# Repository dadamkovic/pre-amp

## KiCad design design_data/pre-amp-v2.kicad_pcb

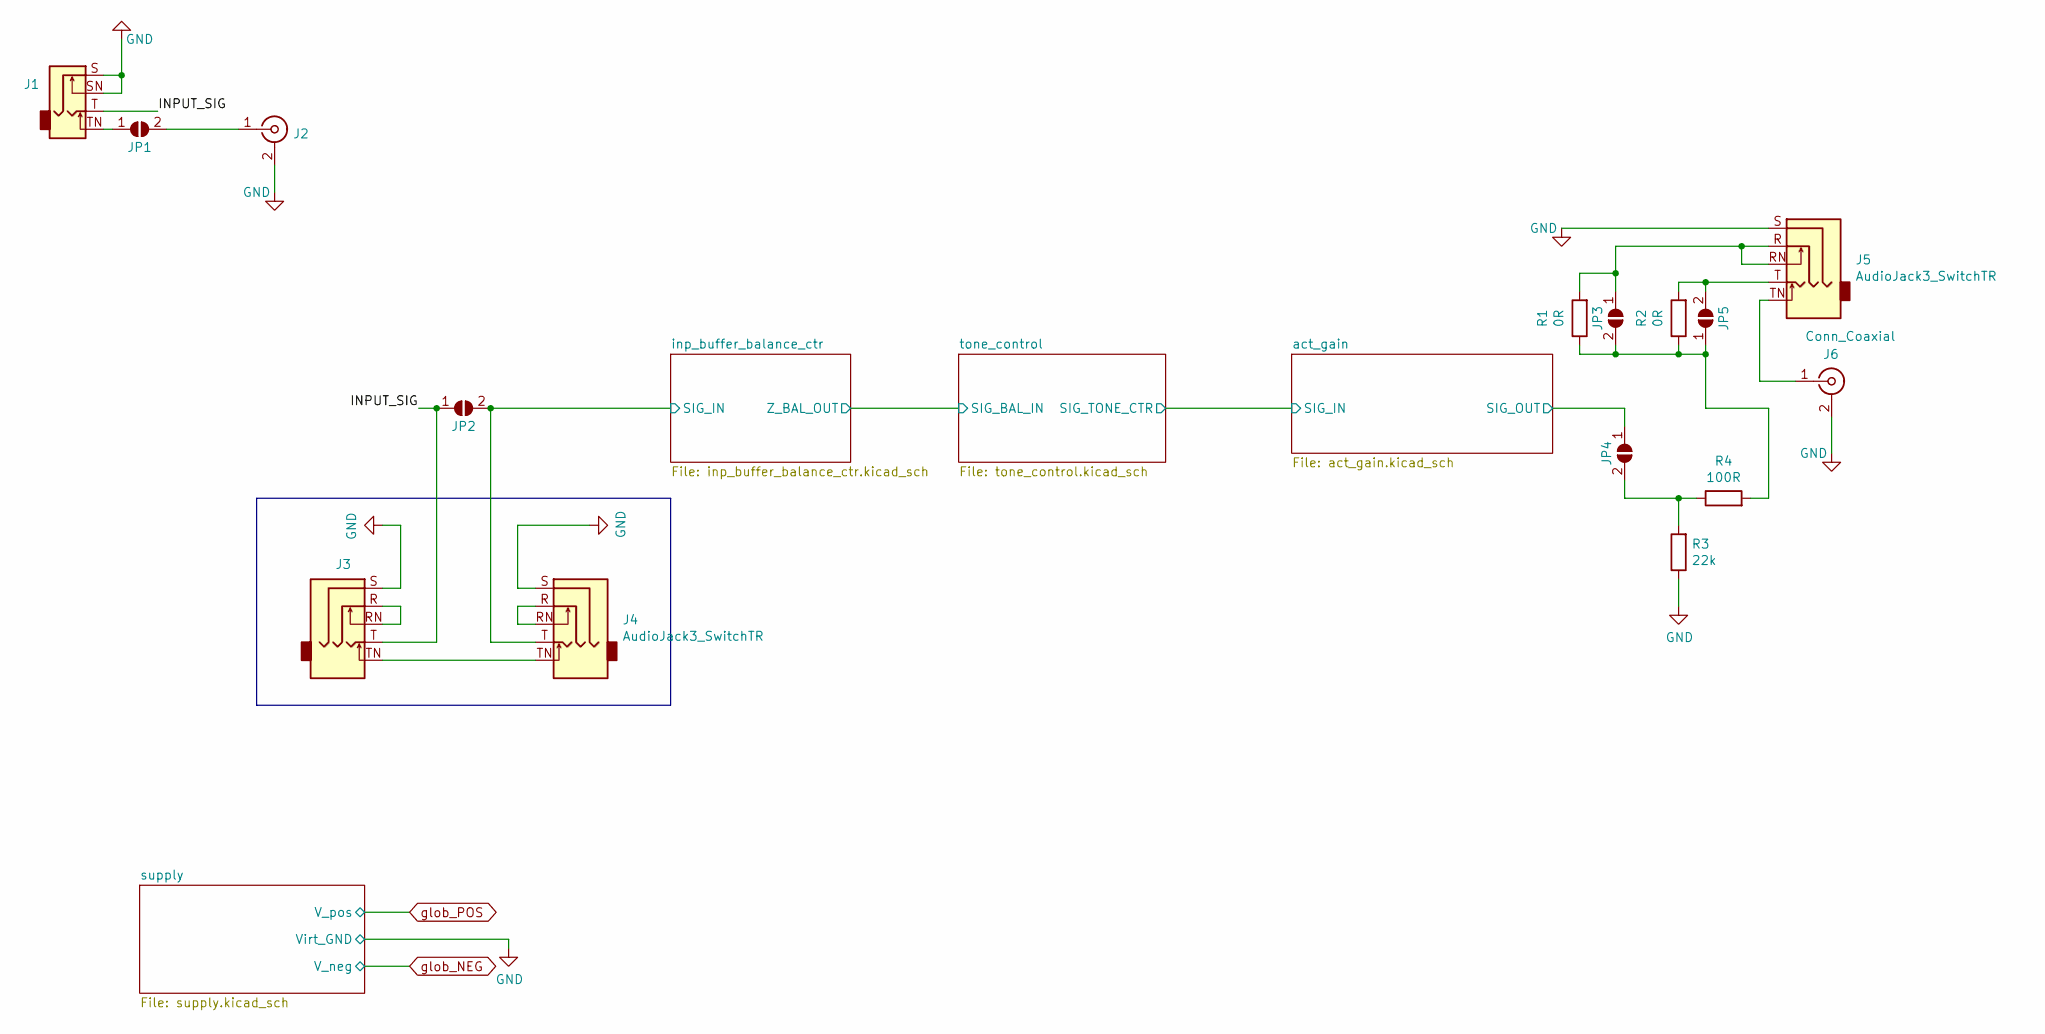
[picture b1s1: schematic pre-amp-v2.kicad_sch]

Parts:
J1: AudioJack2_Switch; Jack_6.35mm_Neutrik_NMJ4HHD2_Horizontal
J2, J6: Conn_Coaxial; 156-0096-E
J3, J4, J5: AudioJack3_SwitchTR; Jack_3.5mm_CUI_SJ1-3535NG_Horizontal
JP1, JP2, JP3, JP4, JP5: SolderJumper_2_Open; SolderJumper-2_P1.3mm_Open_RoundedPad1.0x1.5mm
R1, R2: 0R; R_0805_2012Metric_Pad1.20x1.40mm_HandSolder
R3: 22k; R_0805_2012Metric_Pad1.20x1.40mm_HandSolder
R4: 100R; R_0805_2012Metric_Pad1.20x1.40mm_HandSolder

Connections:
/INPUT_SIG: J1.T, J3.T, JP2.1 (A)
/act_gain/SIG_OUT: JP4.1 (A); also elsewhere on the board
/inp_buffer_balance_ctr/SIG_IN: J4.T, JP2.2 (B); also elsewhere on the board
GND: J1.S, J1.SN, J2.2 (Ext), J3.S, J4.S, J5.S, J6.2 (Ext), R3.1; also elsewhere on the board
unnamed: J1.TN, JP1.1 (A)
unnamed: J2.1 (In), JP1.2 (B)
unnamed: J3.R, J3.RN
unnamed: J3.TN, J4.TN
unnamed: J4.R, J4.RN
unnamed: J5.R, J5.RN, JP3.1 (A), R1.2
unnamed: J5.T, JP5.2 (B), R2.2
unnamed: J5.TN, J6.1 (In)
unnamed: JP3.2 (B), JP5.1 (A), R1.1, R2.1, R4.2
unnamed: JP4.2 (B), R3.2, R4.1

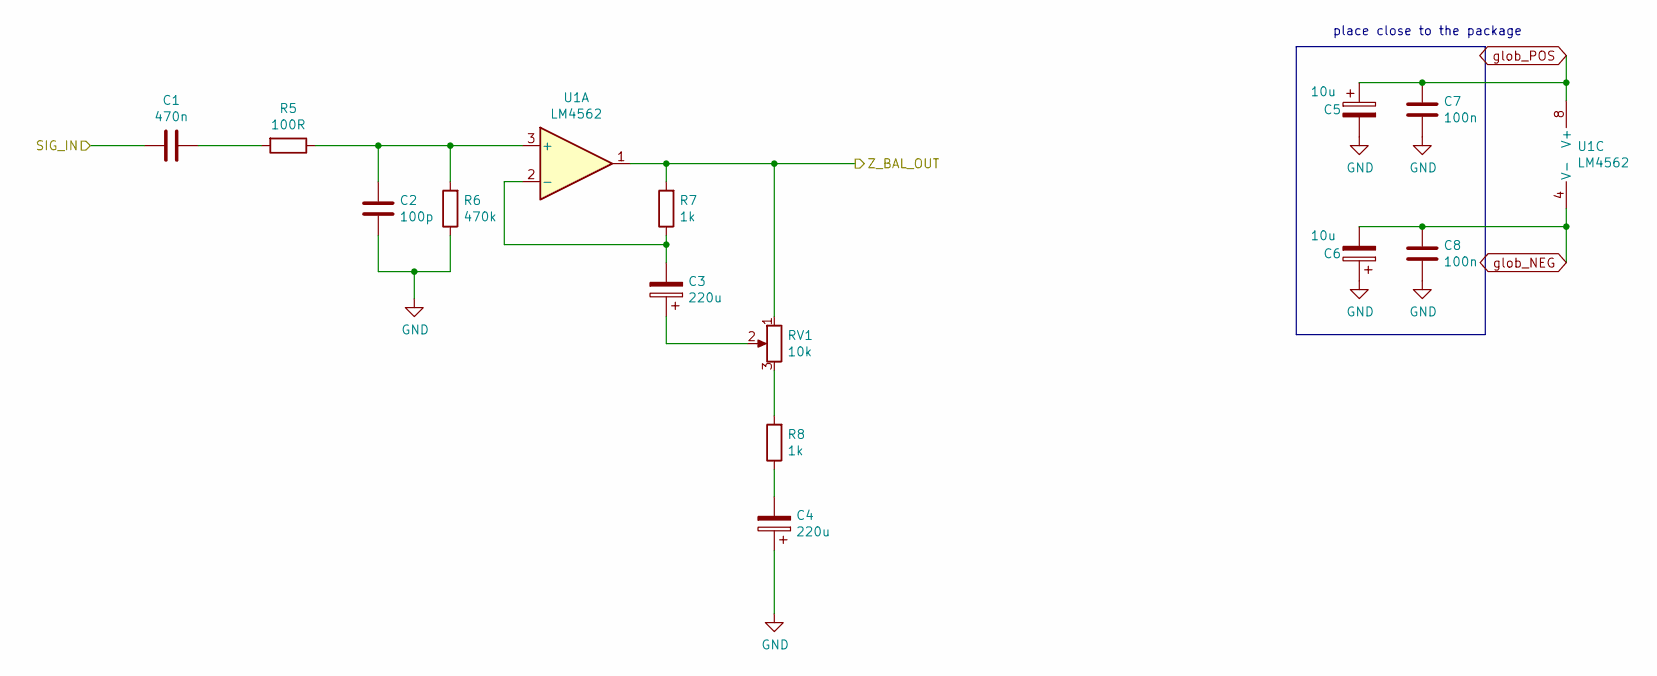
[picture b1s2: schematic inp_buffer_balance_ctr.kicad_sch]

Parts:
C1: 470n; C_Rect_L7.2mm_W3.5mm_P5.00mm_FKS2_FKP2_MKS2_MKP2
C2: 100p; C_0805_2012Metric_Pad1.18x1.45mm_HandSolder
C3, C4: 220u; CP_Radial_D6.3mm_P2.50mm
C5, C6: 10u; CP_Elec_4x5.4
C7, C8: 100n; C_0805_2012Metric_Pad1.18x1.45mm_HandSolder
R5: 100R; R_0805_2012Metric_Pad1.20x1.40mm_HandSolder
R6: 470k; R_0805_2012Metric_Pad1.20x1.40mm_HandSolder
R7, R8: 1k; R_0805_2012Metric_Pad1.20x1.40mm_HandSolder
RV1: 10k; Potentiometer_Bourns_PTV09A-1_Single_Vertical
U1: LM4562; SOIC-8_3.9x4.9mm_P1.27mm

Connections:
/inp_buffer_balance_ctr/SIG_IN: C1.2; also elsewhere on the board
/inp_buffer_balance_ctr/Z_BAL_OUT: R7.2, RV1.1, U1.1; also elsewhere on the board
GND: C2.1, C4.1, C5.2, C6.1, C7.2, C8.2, R6.1; also elsewhere on the board
unnamed: C1.1, R5.2
unnamed: C2.2, R5.1, R6.2, U1.3 (+)
unnamed: C3.1, RV1.2
unnamed: C3.2, R7.1, U1.2 (-)
unnamed: C4.2, R8.1
unnamed: R8.2, RV1.3
glob_NEG: C6.2, C8.1, U1.4 (V-); also elsewhere on the board
glob_POS: C5.1, C7.1, U1.8 (V+); also elsewhere on the board

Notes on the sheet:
place close to the package

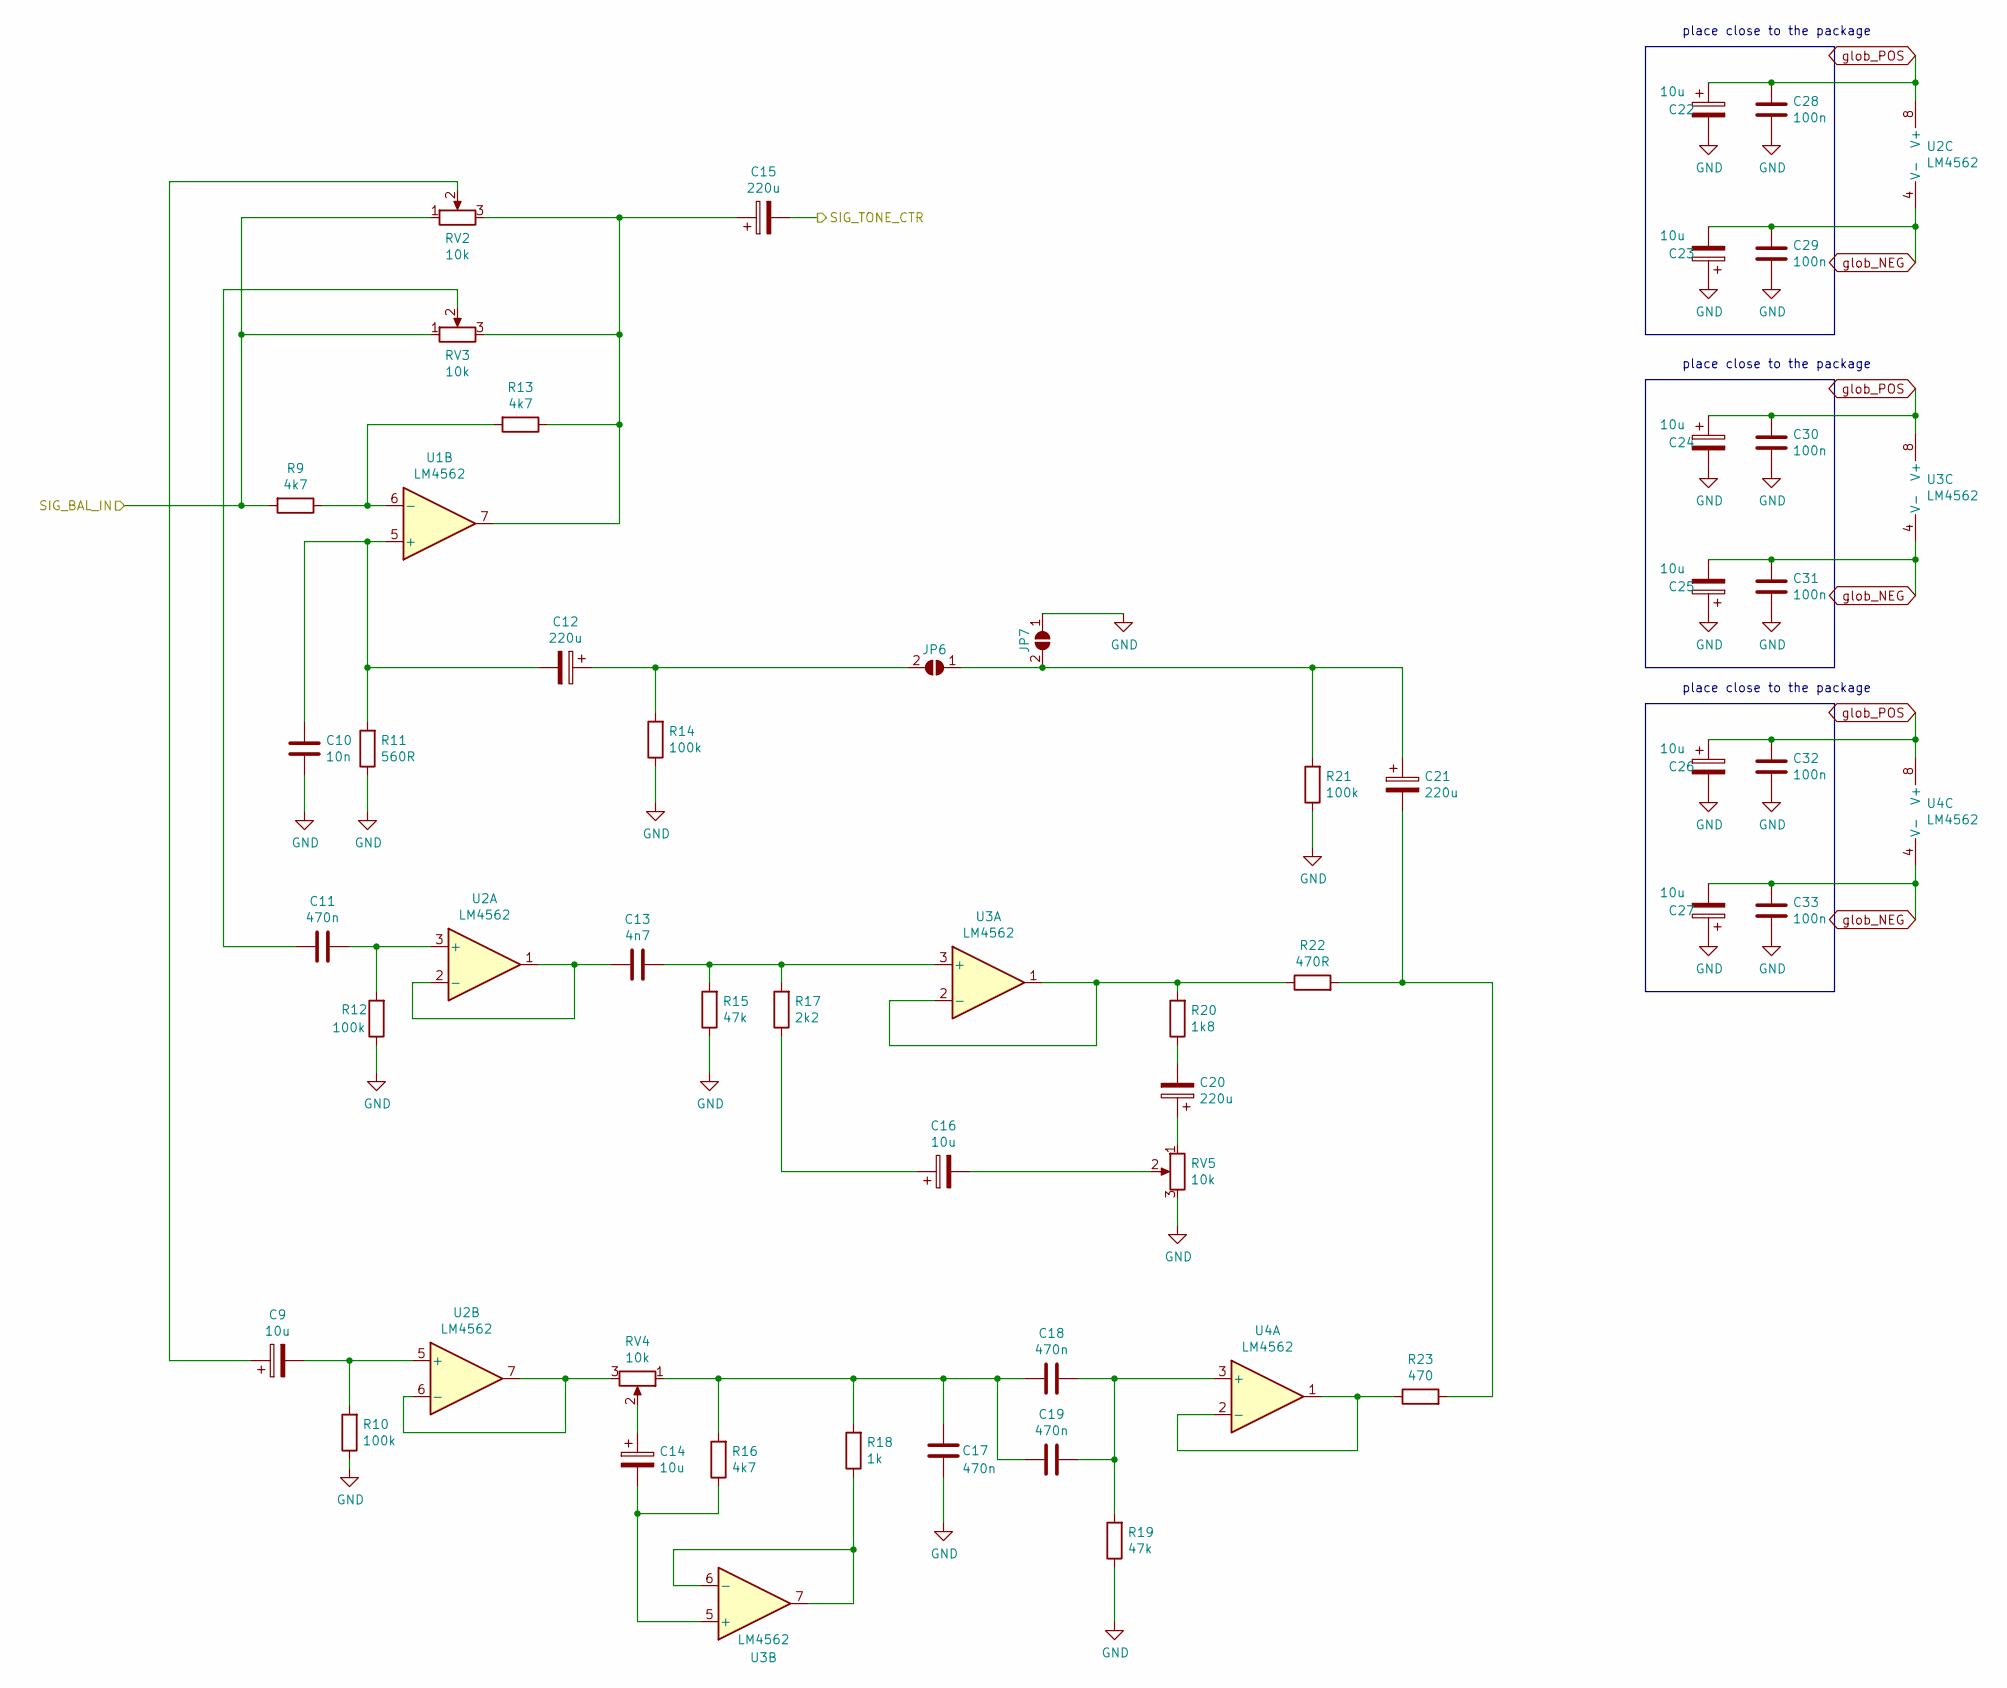
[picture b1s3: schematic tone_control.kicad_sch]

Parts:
C9, C14, C16, C22, C23, C24, C25, C26, C27: 10u; CP_Elec_4x5.4
C10: 10n; C_0805_2012Metric_Pad1.18x1.45mm_HandSolder
C11, C18, C19: 470n; C_Rect_L7.2mm_W3.5mm_P5.00mm_FKS2_FKP2_MKS2_MKP2
C12, C15, C20, C21: 220u; CP_Radial_D6.3mm_P2.50mm
C13: 4n7; C_0805_2012Metric_Pad1.18x1.45mm_HandSolder
C17: 470n; C_0805_2012Metric_Pad1.18x1.45mm_HandSolder
C28, C29, C30, C31, C32, C33: 100n; C_0805_2012Metric_Pad1.18x1.45mm_HandSolder
JP6, JP7: SolderJumper_2_Open; SolderJumper-2_P1.3mm_Open_RoundedPad1.0x1.5mm
R9, R13, R16: 4k7; R_0805_2012Metric_Pad1.20x1.40mm_HandSolder
R10, R12, R14, R21: 100k; R_0805_2012Metric_Pad1.20x1.40mm_HandSolder
R11: 560R; R_0805_2012Metric_Pad1.20x1.40mm_HandSolder
R15, R19: 47k; R_0805_2012Metric_Pad1.20x1.40mm_HandSolder
R17: 2k2; R_0805_2012Metric_Pad1.20x1.40mm_HandSolder
R18: 1k; R_0805_2012Metric_Pad1.20x1.40mm_HandSolder
R20: 1k8; R_0805_2012Metric_Pad1.20x1.40mm_HandSolder
R22: 470R; R_0805_2012Metric_Pad1.20x1.40mm_HandSolder
R23: 470; R_0805_2012Metric_Pad1.20x1.40mm_HandSolder
RV2, RV3: 10k; Potentiometer_Bourns_PTV09A-1_Single_Vertical
RV4, RV5: 10k; Potentiometer_Bourns_PTA6043_Single_Slide
U1, U2, U3, U4: LM4562; SOIC-8_3.9x4.9mm_P1.27mm

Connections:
/act_gain/SIG_IN: C15.2; also elsewhere on the board
/inp_buffer_balance_ctr/Z_BAL_OUT: R9.2, RV2.1, RV3.1; also elsewhere on the board
GND: C10.1, C17.2, C22.2, C23.1, C24.2, C25.1, C26.2, C27.1, C28.2, C29.2, C30.2, C31.2, C32.2, C33.2, JP7.1 (A), R10.1, R11.1, R12.1, R14.1, R15.1, R19.1, R21.1, RV5.3, U4.5 (+); also elsewhere on the board
unnamed: C9.1, RV2.2
unnamed: C9.2, R10.2, U2.5 (+)
unnamed: C10.2, C12.2, R11.2, U1.5 (+)
unnamed: C11.1, RV3.2
unnamed: C11.2, R12.2, U2.3 (+)
unnamed: C12.1, JP6.2 (B), R14.2
unnamed: C13.1, U2.1, U2.2 (-)
unnamed: C13.2, R15.2, R17.2, U3.3 (+)
unnamed: C14.1, RV4.2
unnamed: C14.2, R16.1, U3.5 (+)
unnamed: C16.1, R17.1
unnamed: C16.2, RV5.2
unnamed: C17.1, C18.2, C19.2, R16.2, R18.2, RV4.1
unnamed: C18.1, C19.1, R19.2, U4.3 (+)
unnamed: C20.1, RV5.1
unnamed: C20.2, R20.1
unnamed: C21.1, JP6.1 (A), JP7.2 (B), R21.2
unnamed: C21.2, R22.2, R23.2
unnamed 38: U4.7; also elsewhere on the board
unnamed 39: U4.6 (-); also elsewhere on the board
unnamed: R9.1, R13.2, U1.6 (-)
unnamed: R18.1, U3.6 (-), U3.7
unnamed: R20.2, R22.1, U3.1, U3.2 (-)
unnamed: R23.1, U4.1, U4.2 (-)
unnamed: C15.1, R13.1, RV2.3, RV3.3, U1.7
unnamed: RV4.3, U2.6 (-), U2.7
glob_NEG: C23.2, C25.2, C27.2, C29.1, C31.1, C33.1, U2.4 (V-), U3.4 (V-), U4.4 (V-); also elsewhere on the board
glob_POS: C22.1, C24.1, C26.1, C28.1, C30.1, C32.1, U2.8 (V+), U3.8 (V+), U4.8 (V+); also elsewhere on the board

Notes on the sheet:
place close to the package

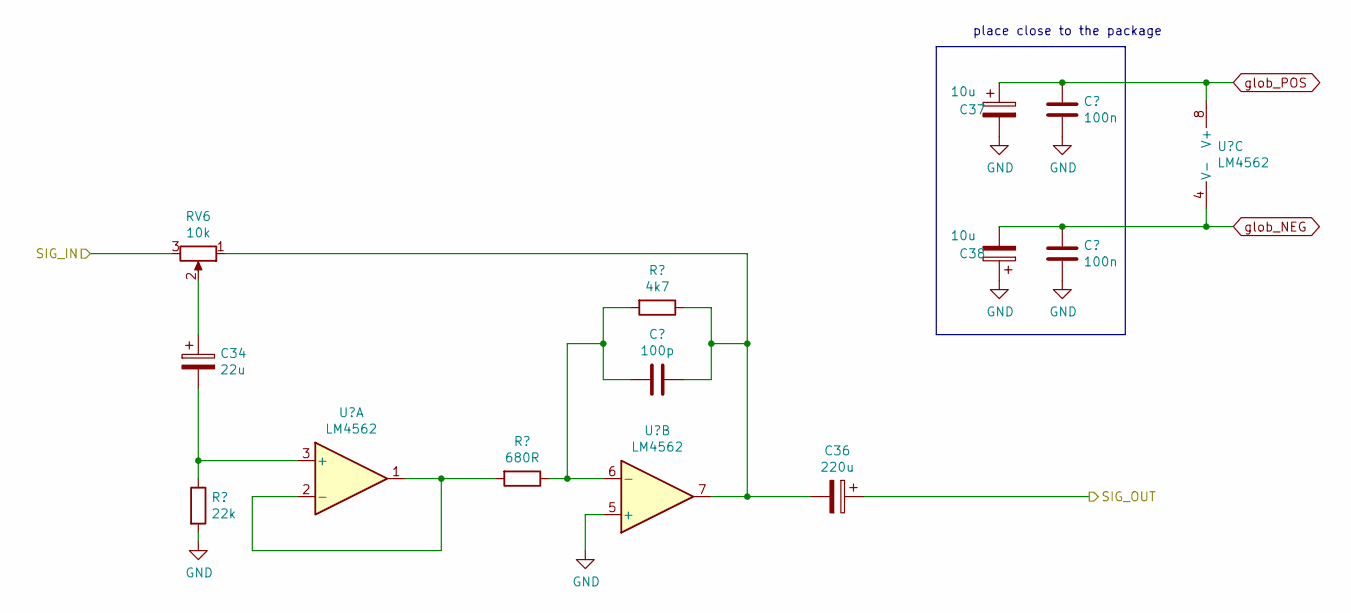
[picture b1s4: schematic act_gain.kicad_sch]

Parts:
C34: 22u; CP_Radial_D5.0mm_P2.00mm
C36: 220u; CP_Radial_D6.3mm_P2.50mm
C37, C38: 10u; CP_Elec_4x5.4
RV6: 10k; Potentiometer_Bourns_PTA6043_Single_Slide

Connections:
/act_gain/SIG_IN: RV6.3; also elsewhere on the board
/act_gain/SIG_OUT: C36.1; also elsewhere on the board
GND: C37.2, C38.1; also elsewhere on the board
unnamed: C34.1, RV6.2
unnamed 37: C34.2; also elsewhere on the board
unnamed 38: C36.2, RV6.1; also elsewhere on the board
glob_NEG: C38.2; also elsewhere on the board
glob_POS: C37.1; also elsewhere on the board

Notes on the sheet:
place close to the package

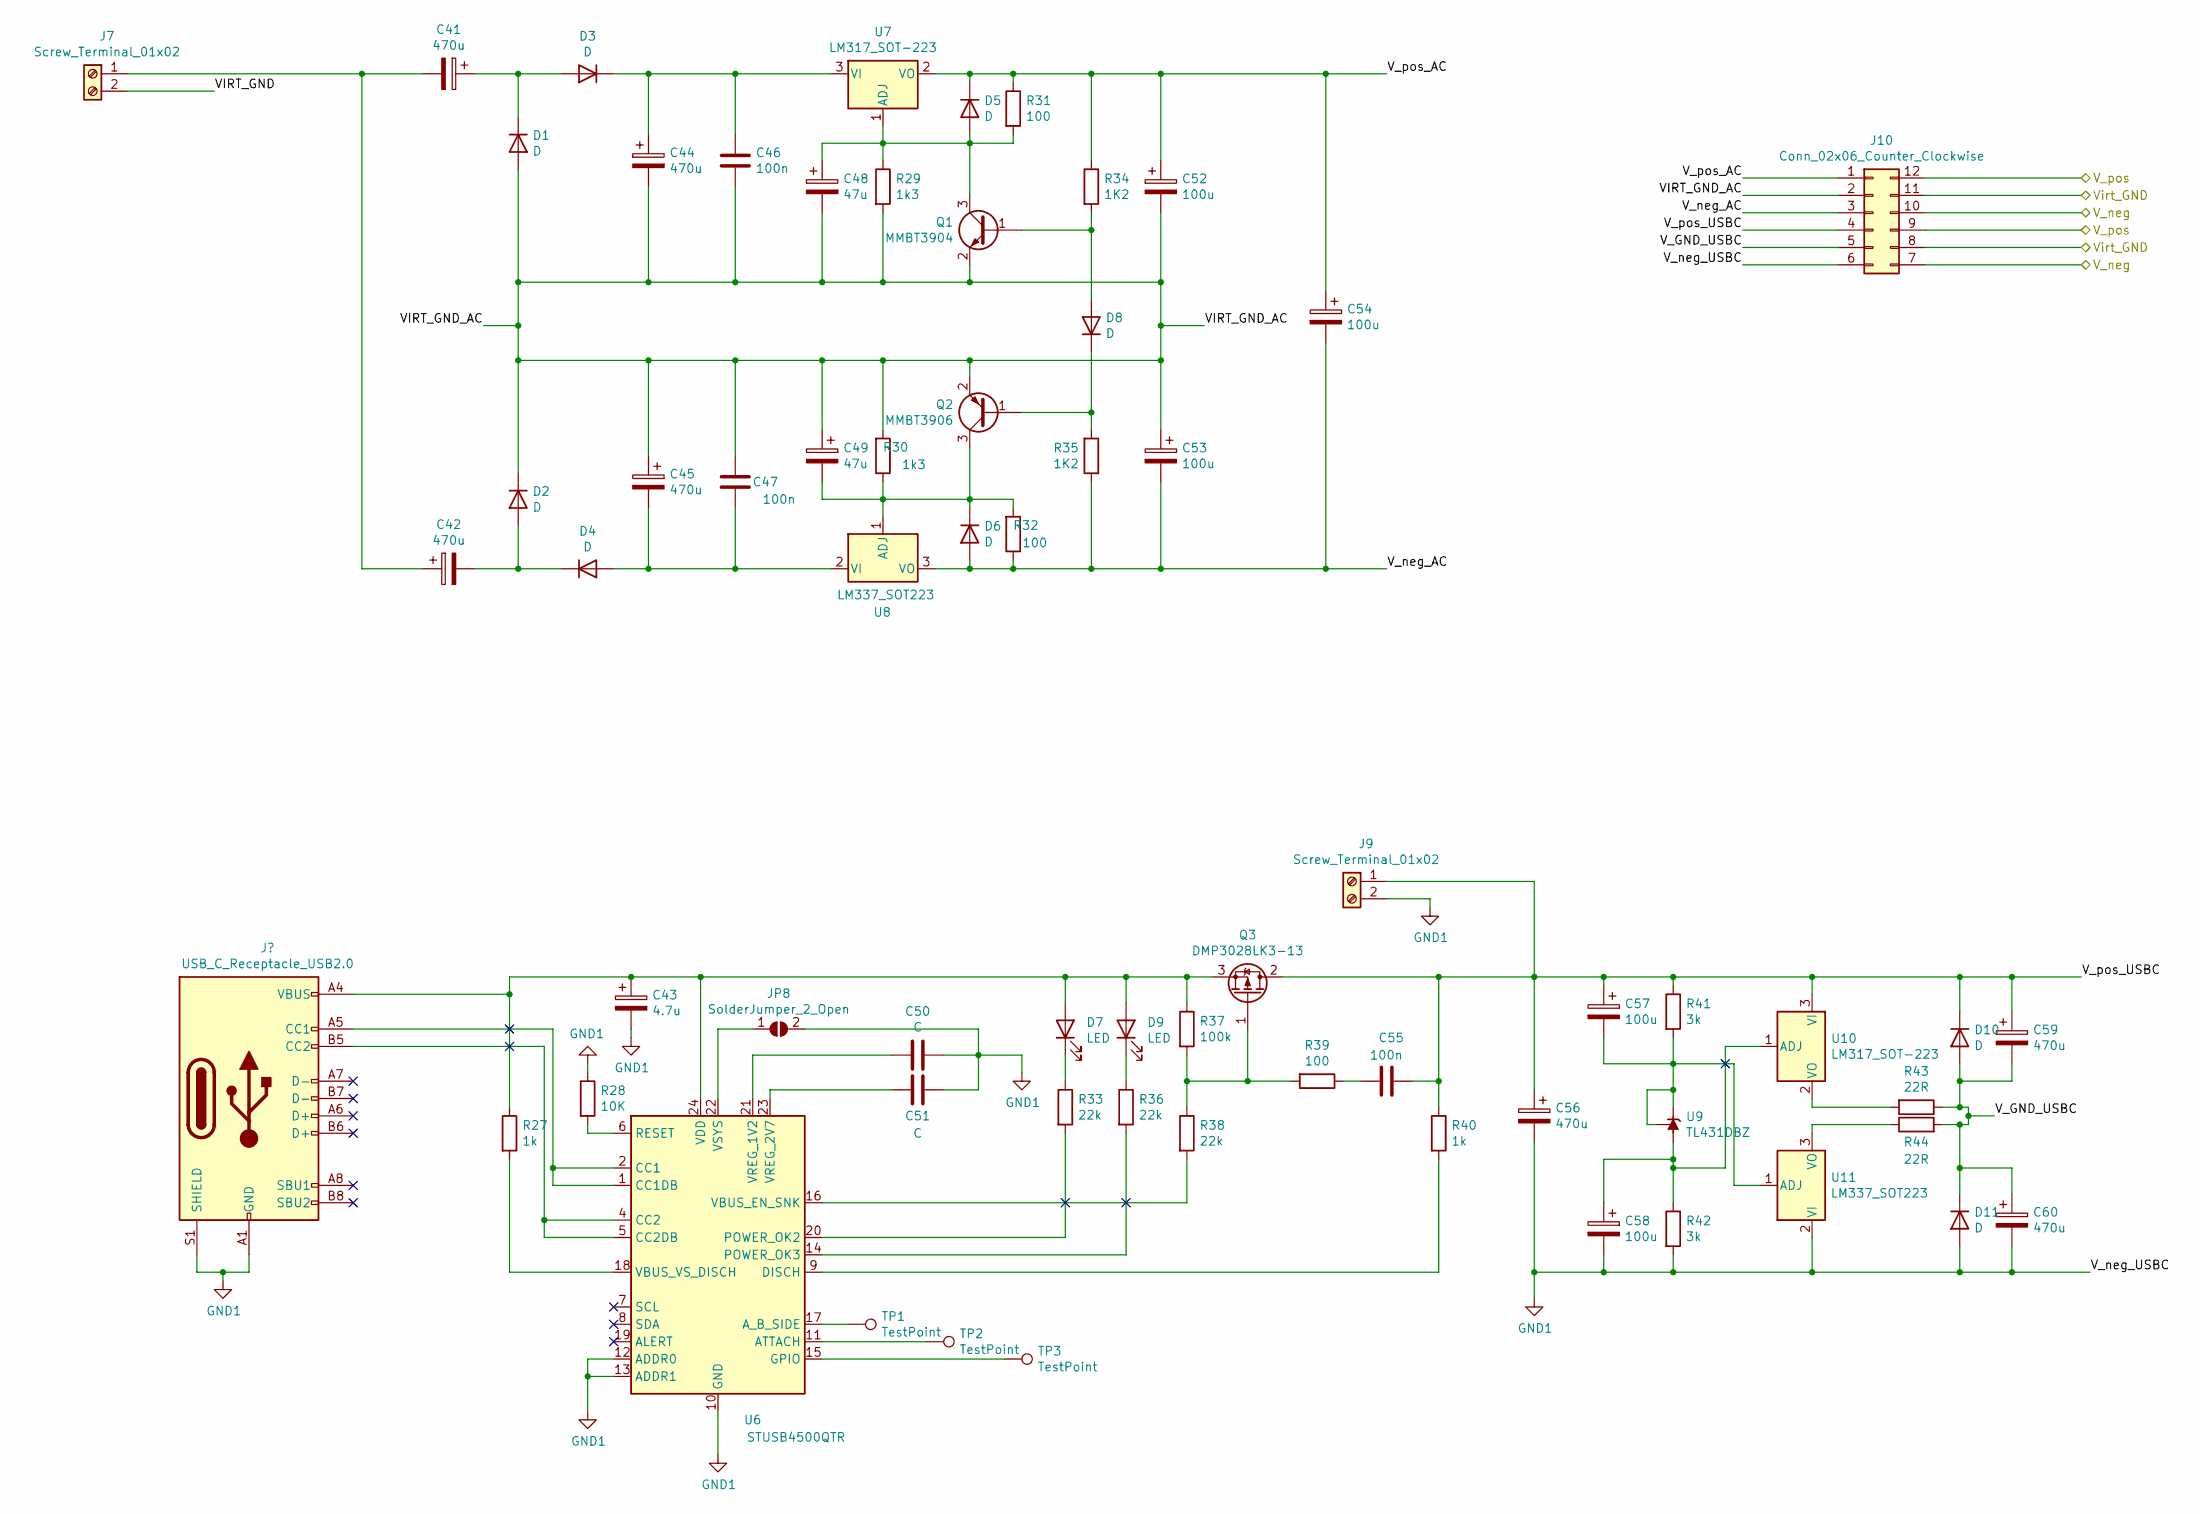
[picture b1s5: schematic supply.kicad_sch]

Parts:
C41, C42, C44, C45, C56, C59, C60: 470u; CP_Radial_D10.0mm_P5.00mm
C43: 4.7u; CP_Elec_5x5.3
C46, C47, C55: 100n; C_0805_2012Metric_Pad1.18x1.45mm_HandSolder
C48, C49: 47u; CP_Radial_D5.0mm_P2.00mm
C50, C51: C; C_0805_2012Metric_Pad1.18x1.45mm_HandSolder
C52, C53, C54, C57, C58: 100u; CP_Radial_D6.3mm_P2.50mm
D1, D2, D3, D4, D5, D6, D8, D10, D11: D; D_SMA_Handsoldering
D7, D9: LED; LED_0805_2012Metric_Pad1.15x1.40mm_HandSolder
J7, J9: Screw_Terminal_01x02; Phoenix_7.62_5.08(02x01)
J10: Conn_02x06_Counter_Clockwise; PinHeader_2x06_P2.54mm_Vertical_SMD
JP8: SolderJumper_2_Open; SolderJumper-2_P1.3mm_Open_RoundedPad1.0x1.5mm
Q1: MMBT3904; SOT-23
Q2: MMBT3906; SOT-23
Q3: DMP3028LK3-13; TO-252-2
R27, R40: 1k; R_0805_2012Metric_Pad1.20x1.40mm_HandSolder
R28: 10K; R_0805_2012Metric_Pad1.20x1.40mm_HandSolder
R29, R30: 1k3; R_0805_2012Metric_Pad1.20x1.40mm_HandSolder
R31, R32, R39: 100; R_0805_2012Metric_Pad1.20x1.40mm_HandSolder
R33, R36, R38: 22k; R_0805_2012Metric_Pad1.20x1.40mm_HandSolder
R34, R35: 1K2; R_0805_2012Metric_Pad1.20x1.40mm_HandSolder
R37: 100k; R_0805_2012Metric_Pad1.20x1.40mm_HandSolder
R41, R42: 3k; R_0805_2012Metric_Pad1.20x1.40mm_HandSolder
R43, R44: 22R; R_0805_2012Metric_Pad1.20x1.40mm_HandSolder
TP1, TP2, TP3: TestPoint; TestPoint_Pad_2.5x2.5mm
U6: STUSB4500QTR; QFN-24-1EP_4x4mm_P0.5mm_EP2.7x2.7mm
U7, U10: LM317_SOT-223; SOT-223-3_TabPin2
U8, U11: LM337_SOT223; SOT-223-3_TabPin2
U9: TL431DBZ; SOT-23

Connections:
/supply/VIRT_GND: J7.2
/supply/VIRT_GND_AC: C44.2, C45.1, C46.2, C47.2, C48.2, C49.1, C52.2, C53.1, D1.2 (A), D2.1 (K), J10.2, Q1.2 (E), Q2.2 (E), R29.2, R30.2
/supply/V_GND_USBC: C59.2, C60.1, D10.2 (A), D11.1 (K), J10.5, R43.1, R44.2
/supply/V_neg_AC: C53.2, C54.2, D6.2 (A), J10.3, R32.1, R35.1, U8.3 (VO)
/supply/V_pos_AC: C52.1, C54.1, D5.1 (K), J10.1, R31.1, R34.1, U7.2 (VO)
/supply/V_pos_USBC: C55.2, C56.1, C57.1, C59.1, D10.1 (K), J9.1, J10.4, Q3.2 (D), R40.1, R41.1, U10.3 (VI)
GND: J10.8, J10.11; also elsewhere on the board
GND1: C43.2, C50.1, C51.1, C56.2, C58.2, C60.2, D11.2 (A), J9.2, J10.6, JP8.2 (B), R28.1, R42.2, U6.10 (GND), U6.12 (ADDR0), U6.13 (ADDR1), U6.25 (GND), U11.2 (VI); also elsewhere on the board
unnamed: C41.1, D1.1 (K), D3.2 (A)
unnamed: C41.2, C42.1, J7.1
unnamed: C42.2, D2.2 (A), D4.1 (K)
unnamed: C44.1, C46.1, D3.1 (K), U7.3 (VI)
unnamed: C45.2, C47.1, D4.2 (A), U8.2 (VI)
unnamed: C48.1, D5.2 (A), Q1.3 (C), R29.1, R31.2, U7.1 (ADJ)
unnamed: C49.2, D6.1 (K), Q2.3 (C), R30.1, R32.2, U8.1 (ADJ)
unnamed: C55.1, R39.1
unnamed: C57.2, R41.2, U9.1 (K), U9.2 (REF), U11.1 (ADJ)
unnamed: C58.1, R42.1, U9.3 (A), U10.1 (ADJ)
unnamed: D7.1 (K), R33.1
unnamed: D8.1 (K), Q2.1 (B), R35.2
unnamed: D8.2 (A), Q1.1 (B), R34.2
unnamed: D9.1 (K), R36.1
unnamed: Q3.1 (G), R37.2, R38.1, R39.2
unnamed: R43.2, U10.2 (VO)
unnamed: R44.1, U11.3 (VO)
unnamed 75: U6.1 (CC1DB), U6.2 (CC1); also elsewhere on the board
unnamed 76: U6.4 (CC2), U6.5 (CC2DB); also elsewhere on the board
unnamed: R28.2, U6.6 (RESET)
unnamed: R40.2, U6.9 (DISCH)
unnamed: TP2.1, U6.11 (ATTACH)
unnamed: R36.2, U6.14 (POWER_OK3)
unnamed: TP3.1, U6.15 (GPIO)
unnamed: R38.2, U6.16 (VBUS_EN_SNK)
unnamed: TP1.1, U6.17 (A_B_SIDE)
unnamed: R27.2, U6.18 (VBUS_VS_DISCH)
unnamed: R33.2, U6.20 (POWER_OK2)
unnamed: C50.2, U6.21 (VREG_1V2)
unnamed: JP8.1 (A), U6.22 (VSYS)
unnamed: C51.2, U6.23 (VREG_2V7)
unnamed 89: C43.1, D7.2 (A), D9.2 (A), Q3.3 (S), R27.1, R37.1, U6.24 (VDD); also elsewhere on the board
glob_NEG: J10.7, J10.10; also elsewhere on the board
glob_POS: J10.9, J10.12; also elsewhere on the board

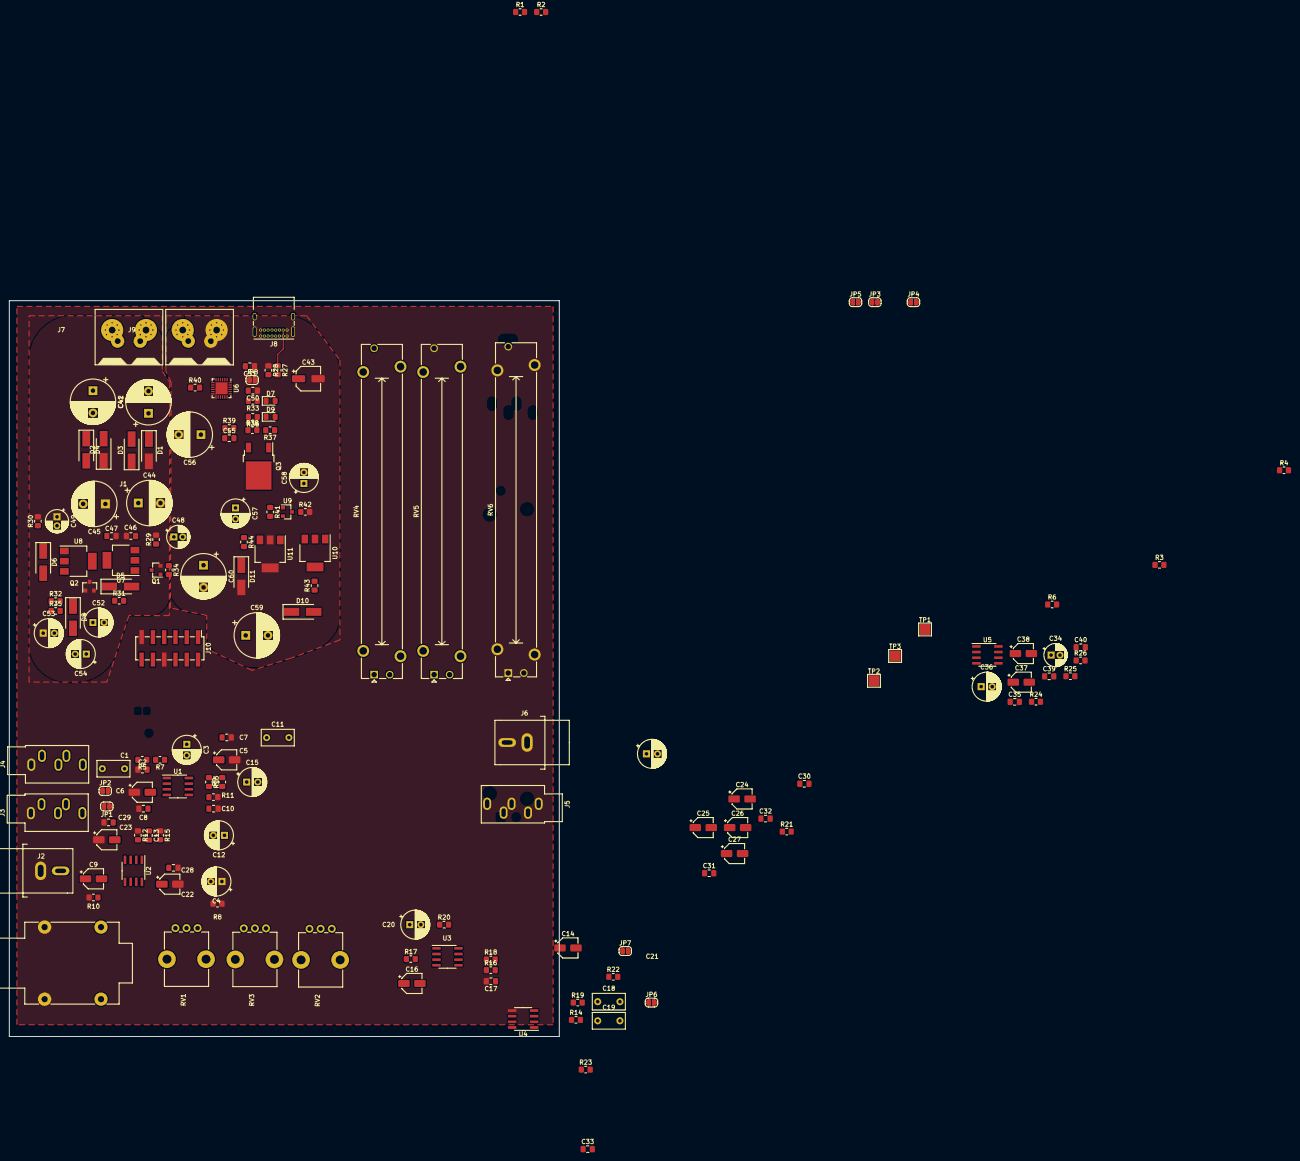
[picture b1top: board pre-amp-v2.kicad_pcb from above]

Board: 2 copper layers, 123.9 x 165.7 mm, 156 parts (0 on the bottom side), 91 nets.

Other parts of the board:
C35: 100p; C_0805_2012Metric_Pad1.18x1.45mm_HandSolder
C39, C40: 100n; C_0805_2012Metric_Pad1.18x1.45mm_HandSolder
J8: USB_C_Receptacle_USB2.0; USB_C_Receptacle_GCT_USB4085
R24: 22k; R_0805_2012Metric_Pad1.20x1.40mm_HandSolder
R25: 680R; R_0805_2012Metric_Pad1.20x1.40mm_HandSolder
R26: 4k7; R_0805_2012Metric_Pad1.20x1.40mm_HandSolder
U5: LM4562; SOIC-8_3.9x4.9mm_P1.27mm

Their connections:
GND: C39.2, C40.2, R24.2; also elsewhere on the board
GND1: J8.A1 (GND), J8.A12 (GND), J8.B1 (GND), J8.B12 (GND), J8.S1 (SHIELD); also elsewhere on the board
unnamed 37: R24.1, U5.3 (+); also elsewhere on the board
unnamed 38: C35.1, R26.1; also elsewhere on the board
unnamed 39: C35.2, R25.1, R26.2; also elsewhere on the board
unnamed: R25.2, U5.1, U5.2 (-)
unnamed 75: J8.A5 (CC1); also elsewhere on the board
unnamed 76: J8.B5 (CC2); also elsewhere on the board
unnamed 89: J8.A4 (VBUS), J8.A9 (VBUS), J8.B4 (VBUS), J8.B9 (VBUS); also elsewhere on the board
glob_NEG: C40.1, U5.4 (V-); also elsewhere on the board
glob_POS: C39.1, U5.8 (V+); also elsewhere on the board

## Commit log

2022-12-18 Initial commit with mostly finished schematic and started layout work.
